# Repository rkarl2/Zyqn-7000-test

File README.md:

# Zynq-7020 Vision Test Board
Test board for the Zynq 7020. This is mainly for my practice/learning more advanced pcb design.

Features:
* USB OTG (Host/Device)
* Ethernet
* On board Programming via JTAG
* HDMI RX
* HDMI TX
* 2x CSI-2 RX
* 1x CSI-2 TX
* 1 Gbit Flash
* SD Card

## Schematics

Full Schmatics [here](./pcb/zynq_test/pdf/Zynqinator.pdf)

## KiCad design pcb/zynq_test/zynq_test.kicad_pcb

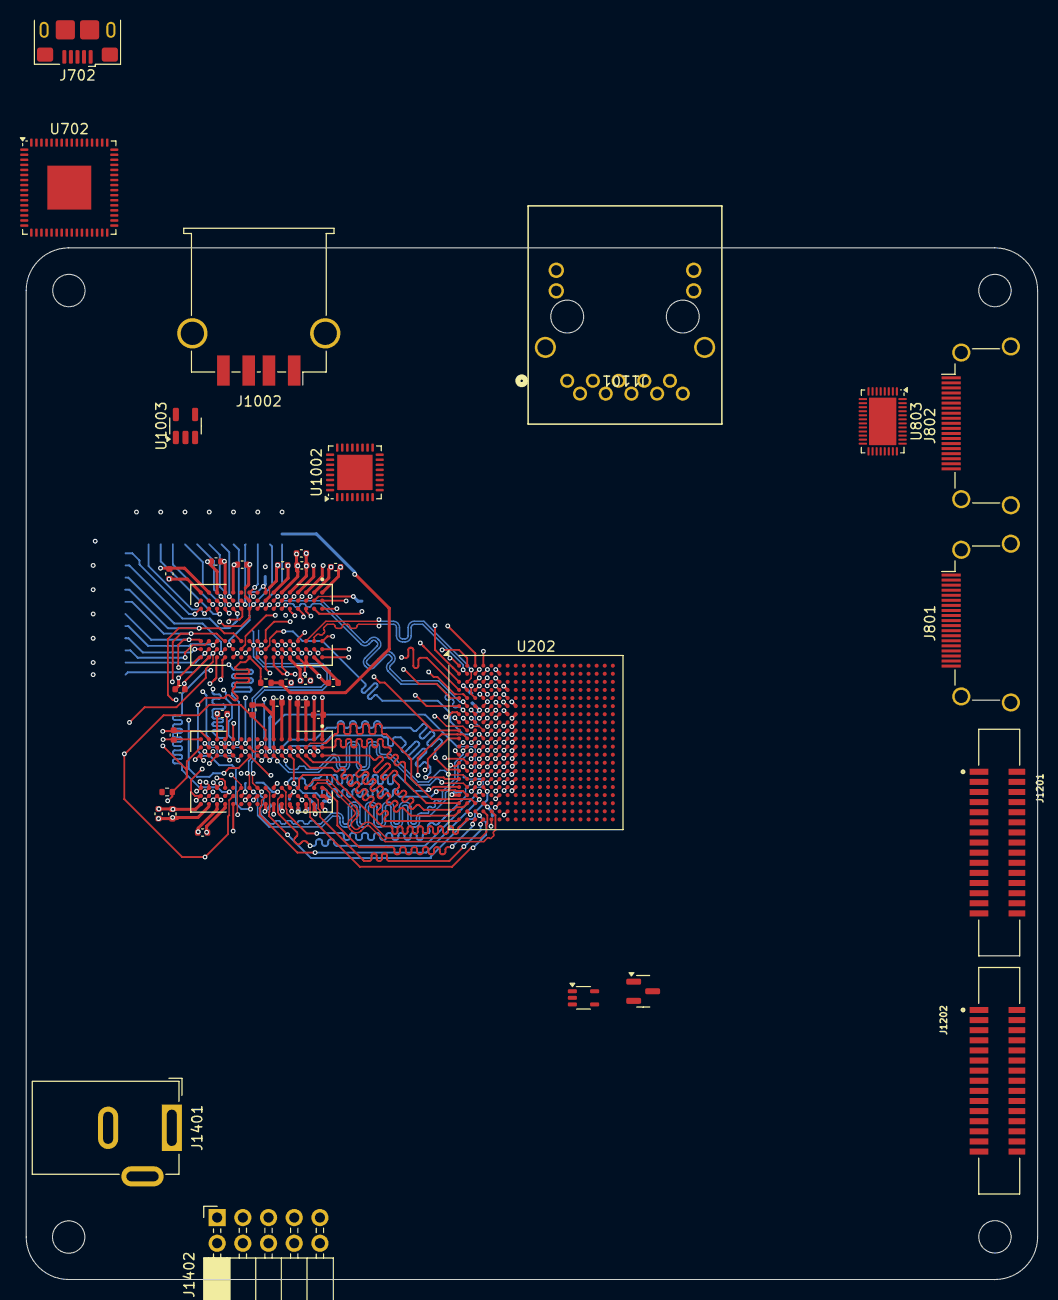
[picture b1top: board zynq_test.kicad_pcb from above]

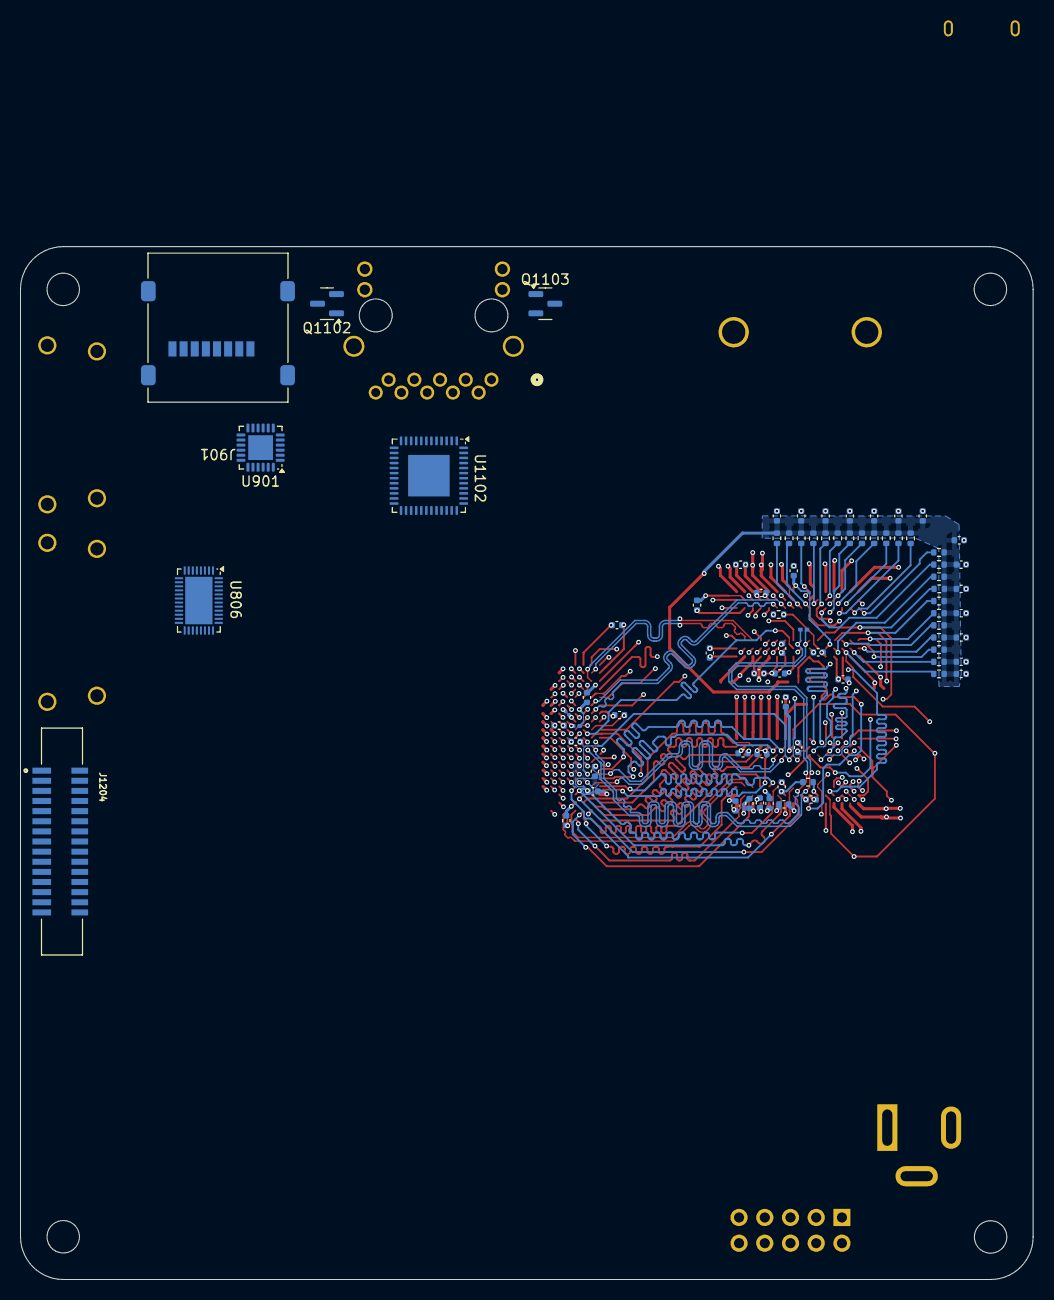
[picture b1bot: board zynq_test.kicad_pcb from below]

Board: 8 copper layers, 100.0 x 102.0 mm, 118 parts (78 on the bottom side), 203 nets.

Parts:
C401, C403, C406, C409, C411, C501, C502, C537, C538, C617, C620, C622, C624: 470n; C_0402_1005Metric
C402, C405, C408, C412, C415, C416, C539, C540, C627, C630: 4u7; C_0402_1005Metric
C404, C407, C410, C413, C414: 100n; C_0402_1005Metric
C503, C504, C505, C506, C507, C508, C509, C510, C511, C512, C513, C514, C515, C516, C517, C518, C519, C520, C521, C522, C523, C524, C525, C526, C527, C528, C530, C532, C533, C534, C535, C536: 47n; C_0402_1005Metric
C529, C531: 10n; C_0402_1005Metric
C632: 100u; C_0402_1005Metric
J702: USB_B_Micro; USB_Micro-B_Amphenol_10118193-0001LF_Horizontal
J801, J802: HDMI_A; HDMI_A_Amphenol_10029449-x01xLF_Horizontal
J901: A-MicroTF-1.85A; microSD_HC_Molex_47219-2001
J1002: USB_A; USB_A_TE_292303-7_Horizontal
J1101: RJ45_JK0654219; ARJM11C7-502-AB-ER2-T_ABR
J1201, J1202, J1204: 1-1734248-5; TE_1-1734248-5
J1401: Barrel_Jack; BarrelJack_GCT_DCJ200-10-A_Horizontal
J1402: Conn_02x05_Odd_Even; PinSocket_2x05_P2.54mm_Horizontal
Q1102, Q1103, Q1104: 2N7002E; SOT-23
R401, R402, R406: 80R; R_0201_0603Metric
R403: 4k7; R_0402_1005Metric
R404, R405: 240R; R_0402_1005Metric
R407, R408, R409, R410, R411, R412, R413, R414, R415, R416, R417, R418, R419, R420, R421, R422, R423, R424, R425, R426, R427, R428, R429, R430: 40R; R_0402_1005Metric
U202: XC7Z020-2CLG400I; Zynq_Z7020-2CLG400I_W_Delay
U401, U402: MT41K256M16TW-107; BGA96C80P9X16_1400X800X120_pinDelays
U702: FT2232HQ; QFN-64-1EP_9x9mm_P0.5mm_EP4.35x4.35mm
U803, U806: TDP1204RNQR; Texas_RNQ0040A_WQFN-40-1EP_6x4mm_P0.4mm_EP4.7x2.7mm
U901: TXS02612RTW; WQFN-24-1EP_4x4mm_P0.5mm_EP2.45x2.45mm
U1002: TUSB1210-Q1; VQFN-32-1EP_5x5mm_P0.5mm_EP3.5x3.5mm
U1003: AP22816AKBWT; SOT-23-5
U1102: LAN8830; VQFN-48-1EP_7x7mm_P0.5mm_EP4.1x4.1mm
U1405: 74LVC1G17; Texas_R-PDSO-G5_DCK-5

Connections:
+1V0: J1402.4, U202.G7 (VCCPINT), U202.G11 (VCCBRAM), U202.G13 (VCCINT), U202.H10 (VCCBRAM), U202.H12 (VCCINT), U202.J7 (VCCPINT), U202.J13 (VCCINT), U202.K12 (VCCINT), U202.L7 (VCCPINT), U202.L13 (VCCINT), U202.M12 (VCCINT), U202.N7 (VCCPINT), U202.N13 (VCCINT), U202.P8 (VCCPINT), U202.P12 (VCCINT), U202.R7 (VCCPINT), U202.R13 (VCCINT)
+1V8: J1402.6, U202.A13 (VCCO_MIO1_501), U202.B16 (VCCO_MIO1_501), U202.D12 (VCCO_MIO1_501), U202.E15 (VCCO_MIO1_501), U202.F8 (VCCPAUX), U202.G9 (VCCPAUX), U202.H8 (VCCPAUX), U202.J9 (VCCADC_0), U202.J11 (VCCAUX), U202.K8 (VCCPAUX), U202.L11 (VCCAUX), U202.M8 (VCCPAUX), U202.N9 (VCCAUX), U202.N11 (VCCAUX), U202.P10 (VCCAUX), U202.R9 (VCCAUX), U202.T8 (VCCO_13), U202.U11 (VCCO_13), U202.W7 (VCCO_13), U202.Y10 (VCCO_13), U901.5 (V_{CCA}), U1002.11 (CS), U1002.14 (CFG), U1002.27 (RESETB), U1002.28 (V_{DD18}), U1002.30 (V_{DD18}), U1002.32 (V_{DDIO}), U1102.17 (VDDIO), U1102.24 (VDDIO), U1102.28 (VDDIO), U1102.35 (VDDIO), U1102.41 (VDDIO)
+1V8_FTDI: U702.12 (VCORE), U702.37 (VCORE), U702.49 (VREGOUT), U702.64 (VCORE)
+1V35: C501.1, C502.1, C503.1, C504.1, C505.1, C506.1, C507.1, C508.1, C509.1, C510.1, C511.1, C512.1, C513.1, C514.1, C515.1, C516.1, C517.1, C518.1, C519.1, C520.1, C521.1, C522.1, C523.1, C524.1, C525.1, C526.1, C527.1, C528.1, C530.1, C532.1, C533.1, C534.1, C535.1, C536.1, C537.1, C538.1, C539.1, C540.1, C617.1, C620.1, C622.1, C624.1, C627.1, C630.1, C632.1, J1402.8, R401.1, U202.A3 (VCCO_DDR_502), U202.D2 (VCCO_DDR_502), U202.E5 (VCCO_DDR_502), U202.G1 (VCCO_DDR_502), U202.H4 (VCCO_DDR_502), U202.L3 (VCCO_DDR_502), U202.P2 (VCCO_DDR_502), U202.R5 (VCCO_DDR_502), U202.U1 (VCCO_DDR_502), U202.V4 (VCCO_DDR_502), U401.A1 (VDDQ), U401.A8 (VDDQ), U401.B2 (VDD), U401.C1 (VDDQ), U401.C9 (VDDQ), U401.D2 (VDDQ), U401.D9 (VDD), U401.E9 (VDDQ), U401.F1 (VDDQ), U401.G7 (VDD), U401.H2 (VDDQ), U401.H9 (VDDQ), U401.K2 (VDD), U401.K8 (VDD), U401.N1 (VDD), U401.N9 (VDD), U401.R1 (VDD), U401.R9 (VDD), U402.A1 (VDDQ), U402.A8 (VDDQ), U402.B2 (VDD), U402.C1 (VDDQ), U402.C9 (VDDQ), U402.D2 (VDDQ), U402.D9 (VDD), U402.E9 (VDDQ), U402.F1 (VDDQ), U402.G7 (VDD), U402.H2 (VDDQ), U402.H9 (VDDQ), U402.K2 (VDD), U402.K8 (VDD), U402.N1 (VDD), U402.N9 (VDD), U402.R1 (VDD), U402.R9 (VDD)
+3V3: J901.4 (VDD), J1101.11 (L_LED_A), J1101.13 (R_LED_A), J1201.15, J1201.15_1 (15__1), J1202.15, J1202.15_1 (15__1), J1204.15, J1204.15_1 (15__1), J1402.10, U202.B6 (VCCO_MIO0_500), U202.C19 (VCCO_35), U202.D7 (VCCO_MIO0_500), U202.F18 (VCCO_35), U202.H14 (VCCO_35), U202.J17 (VCCO_35), U202.K6 (VCCO_0), U202.K20 (VCCO_35), U202.M6 (CFGBVS_0), U202.M16 (VCCO_35), U202.N6 (RSVDVCC3), U202.N19 (VCCO_34), U202.R6 (RSVDVCC2), U202.R15 (VCCO_34), U202.T6 (RSVDVCC1), U202.T18 (VCCO_34), U202.V14 (VCCO_34), U202.W17 (VCCO_34), U202.Y20 (VCCO_34), U702.20 (VCCIO), U702.31 (VCCIO), U702.42 (VCCIO), U702.50 (VREGIN), U702.56 (VCCIO), U803.1 (VCC), U803.6 (VCC), U803.14 (VIO), U803.20 (VCC), U803.28 (VCC), U806.1 (VCC), U806.6 (VCC), U806.14 (VIO), U806.20 (VCC), U806.28 (VCC), U901.17 (VCC_{B1}), U901.21 (VCC_{B0}), U1002.20 (V_{DD33}), U1002.21 (V_{BAT}), U1405.5 (VCC)
+5V: J801.18 (+5V), J802.18 (+5V), J1402.2, U1003.3 (IN)
+5V_{USB_OTG}: J1002.1 (VBUS), U1002.22 (V_{BUS}), U1003.1 (OUT), U1003.5 (OUT)
+V_{TT} 0V675: C402.1, C403.1, C404.1, C405.1, C406.1, C407.1, C408.1, C409.1, C410.1, C411.1, C412.1, C413.1, C414.1, C415.1, C416.1, R407.1, R408.1, R409.1, R410.1, R411.1, R412.1, R413.1, R414.1, R415.1, R416.1, R417.1, R418.1, R419.1, R420.1, R421.1, R422.1, R423.1, R424.1, R425.1, R426.1, R427.1, R428.1, R429.1, R430.1
/Boot/SD0.CLK: J901.5 (CLK), U901.9 (CLKA), U901.19 (CLK_{B0})
/Boot/SD0.CMD: J901.3 (CMD), U202.C17 (PS_MIO41_501), U901.4 (CMDA), U901.20 (CMD_{B0})
/Boot/SD0.DAT0: J901.7 (DAT0), U901.18 (DAT0_{B0})
/Boot/SD0.DAT1: J901.8 (DAT1), U901.16 (DAT1_{B0})
/Boot/SD0.DAT2: J901.1 (DAT2), U901.23 (DAT2_{B0})
/Boot/SD0.DAT3: J901.2 (DAT3/CD), U901.22 (DAT3_{B0})
/Boot/SD0.DATA-0: U202.E12 (PS_MIO42_501), U901.6 (DAT0A)
/Boot/SD0.DATA-1: U202.A9 (PS_MIO43_501), U901.7 (DAT1A)
/Boot/SD0.DATA-2: U202.F13 (PS_MIO44_501), U901.1 (DAT2A)
/Boot/SD0.DATA-3: U202.B15 (PS_MIO45_501), U901.3 (DAT3A)
/Cameras/CAM0.GPIO1.: J1201.11, J1201.11_1 (11__1), J1201.12, J1201.12_1 (12__1)
/Cameras/CAM1.GPIO1.: J1202.11, J1202.11_1 (11__1), J1202.12, J1202.12_1 (12__1)
/Cameras/CAM2.GPIO1.: J1204.11, J1204.11_1 (11__1), J1204.12, J1204.12_1 (12__1)
/Cameras/CAM2.TX.0_N: J1204.2, J1204.2_1 (2__1)
/Cameras/CAM2.TX.0_P: J1204.3, J1204.3_1 (3__1)
/Cameras/CAM2.TX.1_N: J1204.5, J1204.5_1 (5__1)
/Cameras/CAM2.TX.1_P: J1204.6, J1204.6_1 (6__1)
/Cameras/CAM2.TX.CLK_N: J1204.8, J1204.8_1 (8__1)
/Cameras/CAM2.TX.CLK_P: J1204.9, J1204.9_1 (9__1)
/Cameras/CAM_RX.0.CAM_CLK_N: J1201.8, J1201.8_1 (8__1), U202.L20 (IO_L9N_T1_DQS_AD3N_35)
/Cameras/CAM_RX.0.CAM_CLK_P: J1201.9, J1201.9_1 (9__1), U202.L19 (IO_L9P_T1_DQS_AD3P_35)
/Cameras/CAM_RX.0.CAM_D0_N: J1201.2, J1201.2_1 (2__1), U202.F20 (IO_L15N_T2_DQS_AD12N_35)
/Cameras/CAM_RX.0.CAM_D0_P: J1201.3, J1201.3_1 (3__1), U202.F19 (IO_L15P_T2_DQS_AD12P_35)
/Cameras/CAM_RX.0.CAM_D1_N: J1201.5, J1201.5_1 (5__1), U202.H20 (IO_L17N_T2_AD5N_35)
/Cameras/CAM_RX.0.CAM_D1_P: J1201.6, J1201.6_1 (6__1), U202.J20 (IO_L17P_T2_AD5P_35)
/Cameras/CAM_RX.0.I2C_CLK: J1201.13, J1201.13_1 (13__1), U202.K17 (IO_L12P_T1_MRCC_35)
/Cameras/CAM_RX.0.I2C_SDA: J1201.14, J1201.14_1 (14__1), U202.K18 (IO_L12N_T1_MRCC_35)
/Cameras/CAM_RX.1.CAM_CLK_N: J1202.8, J1202.8_1 (8__1), U202.W15 (IO_L10N_T1_34)
/Cameras/CAM_RX.1.CAM_CLK_P: J1202.9, J1202.9_1 (9__1), U202.V15 (IO_L10P_T1_34)
/Cameras/CAM_RX.1.CAM_D0_N: J1202.2, J1202.2_1 (2__1), U202.Y19 (IO_L17N_T2_34)
/Cameras/CAM_RX.1.CAM_D0_P: J1202.3, J1202.3_1 (3__1), U202.Y18 (IO_L17P_T2_34)
/Cameras/CAM_RX.1.CAM_D1_N: J1202.5, J1202.5_1 (5__1), U202.Y17 (IO_L7N_T1_34)
/Cameras/CAM_RX.1.CAM_D1_P: J1202.6, J1202.6_1 (6__1), U202.Y16 (IO_L7P_T1_34)
/Cameras/CAM_RX.1.I2C_CLK: J1202.13, J1202.13_1 (13__1), U202.V20 (IO_L16P_T2_34)
/Cameras/CAM_RX.1.I2C_SDA: J1202.14, J1202.14_1 (14__1), U202.W20 (IO_L16N_T2_34)
/Cameras/CAM_TX.2.I2C_CLK: J1204.13, J1204.13_1 (13__1), U202.T14 (IO_L5P_T0_34)
/Cameras/CAM_TX.2.I2C_SDA: J1204.14, J1204.14_1 (14__1), U202.T15 (IO_L5N_T0_34)
/ETHERNET/ETH0.MDC: U202.C10 (PS_MIO52_501), U1102.37 (MDC)
/ETHERNET/ETH0.MDIO: U202.C11 (PS_MIO53_501), U1102.38 (MDIO)
/ETHERNET/ETH0_INT: U202.K14 (IO_L20P_T3_AD6P_35), U1102.39 (INT_N/GPIO5)
/ETHERNET/ETH_1V1: U1102.4 (VDDAL), U1102.9 (VDDAL), U1102.47 (VDDAL_PLL)
/ETHERNET/ETH_A_3V3: U1102.1 (VDDAH), U1102.12 (VDDAH)
/ETHERNET/ETH_TX1_N: J1101.2 (TRD1-), U1102.3 (TXRXM_A)
/ETHERNET/ETH_TX1_P: J1101.1 (TRD1+), U1102.2 (TXRXP_A)
/ETHERNET/ETH_TX2_N: J1101.4 (TRD2-), U1102.6 (TXRXM_B)
/ETHERNET/ETH_TX2_P: J1101.3 (TRD2+), U1102.5 (TXRXP_B)
/ETHERNET/ETH_TX3_N: J1101.8 (TRD3-), U1102.8 (TXRXM_C)
/ETHERNET/ETH_TX3_P: J1101.7 (TRD3+), U1102.7 (TXRXP_C)
/ETHERNET/ETH_TX4_N: J1101.10 (TRD4-), U1102.11 (TXRXM_D)
/ETHERNET/ETH_TX4_P: J1101.9 (TRD4+), U1102.10 (TXRXP_D)
/ETHERNET/ETH_VDD_1V1: U1102.23 (VDD), U1102.27 (VDD), U1102.31 (VDD), U1102.40 (VDD)
/HDMI/HDMI.CTR.SCL: U202.J16 (IO_L24N_T3_AD15N_35), U803.21 (SCL/CFG0), U806.21 (SCL/CFG0)
/HDMI/HDMI.CTR.SDA: U202.K16 (IO_L24P_T3_AD15P_35), U803.22 (SDA/CFG1), U806.22 (SDA/CFG1)
/HDMI/HDMI.EN: U202.L16 (IO_L11P_T1_SRCC_35), U803.7 (EN), U806.7 (EN)
/HDMI/HDMI.RX.CLK_N: U202.G18 (IO_L16N_T2_35), U806.30 (OUT_CLKN)
/HDMI/HDMI.RX.CLK_P: U202.G17 (IO_L16P_T2_35), U806.31 (OUT_CLKP)
/HDMI/HDMI.RX.D0_N: U202.G15 (IO_L19N_T3_VREF_35), U806.33 (OUT_D0N)
/HDMI/HDMI.RX.D0_P: U202.H15 (IO_L19P_T3_35), U806.34 (OUT_D0P)
/HDMI/HDMI.RX.D1_N: U202.F17 (IO_L6N_T0_VREF_35), U806.36 (OUT_D1N)
/HDMI/HDMI.RX.D1_P: U202.F16 (IO_L6P_T0_35), U806.37 (OUT_D1P)
/HDMI/HDMI.RX.D2_N: U202.D18 (IO_L3N_T0_DQS_AD1N_35), U806.39 (OUT_D2N)
/HDMI/HDMI.RX.D2_P: U202.E17 (IO_L3P_T0_DQS_AD1P_35), U806.40 (OUT_D2P)
/HDMI/HDMI.RX.SCL: U202.J18 (IO_L14P_T2_AD4P_SRCC_35), U806.24 (LV_DDC_SCL)
/HDMI/HDMI.RX.SDA: U202.H18 (IO_L14N_T2_AD4N_SRCC_35), U806.25 (LV_DDC_SDA)
/HDMI/HDMI.TX.CLK_N: U202.E19 (IO_L5N_T0_AD9N_35), U803.19 (IN_CLKN)
/HDMI/HDMI.TX.CLK_P: U202.E18 (IO_L5P_T0_AD9P_35), U803.18 (IN_CLKP)
/HDMI/HDMI.TX.D0_N: U202.D20 (IO_L4N_T0_35), U803.16 (IN_D0N)
/HDMI/HDMI.TX.D0_P: U202.D19 (IO_L4P_T0_35), U803.15 (IN_D0P)
/HDMI/HDMI.TX.D1_N: U202.B20 (IO_L1N_T0_AD0N_35), U803.13 (IN_D1N)
/HDMI/HDMI.TX.D1_P: U202.C20 (IO_L1P_T0_AD0P_35), U803.12 (IN_D1P)
/HDMI/HDMI.TX.D2_N: U202.A20 (IO_L2N_T0_AD8N_35), U803.10 (IN_D2N)
/HDMI/HDMI.TX.D2_P: U202.B19 (IO_L2P_T0_AD8P_35), U803.9 (IN_D2P)
/HDMI/HDMI.TX.HDP: U202.J14 (IO_L20N_T3_AD6N_35), U803.32 (HPD_IN)
/HDMI/HDMI.TX.SCL: U202.G14 (IO_0_35), U803.24 (LV_DDC_SCL)
/HDMI/HDMI.TX.SDA: U202.J15 (IO_25_35), U803.25 (LV_DDC_SDA)
/HDMI/HDMI_SHIELD: J801.SH, J802.SH
/Power/PWR_ON_RST: Q1104.1 (G), U202.C7 (PS_POR_B_500), U1405.4
/Programmer/FTDI_D+: J702.3 (D+), U702.8 (DP)
/Programmer/FTDI_D-: J702.2 (D-), U702.7 (DM)
/USB_OTG/USB0.DATA-0: U202.A14 (PS_MIO32_501), U1002.3 (DATA0)
/USB_OTG/USB0.DATA-1: U202.D15 (PS_MIO33_501), U1002.4 (DATA1)
/USB_OTG/USB0.DATA-2: U202.A12 (PS_MIO34_501), U1002.5 (DATA2)
/USB_OTG/USB0.DATA-3: U202.F12 (PS_MIO35_501), U1002.6 (DATA3)
/USB_OTG/USB0.DATA-4: U202.C16 (PS_MIO28_501), U1002.7 (DATA4)
/USB_OTG/USB0.DATA-5: U202.A10 (PS_MIO37_501), U1002.9 (DATA5)
/USB_OTG/USB0.DATA-6: U202.E13 (PS_MIO38_501), U1002.10 (DATA6)
/USB_OTG/USB0.DATA-7: U202.C18 (PS_MIO39_501), U1002.13 (DATA7)
/USB_OTG/USB0.DIR: U202.C13 (PS_MIO29_501), U1002.31 (DIR)
/USB_OTG/USB0.NXT: U202.E16 (PS_MIO31_501), U1002.2 (NXT)
/USB_OTG/USB0.STP: U202.C15 (PS_MIO30_501), U1002.29 (STP)
/USB_OTG/USB_OTG.D+: J1002.3 (D+), U1002.18 (DP)
/USB_OTG/USB_OTG.D-: J1002.2 (D-), U1002.19 (DM)
/Zynq Dram/DDR_ADDR0: R407.2, U202.N2 (PS_DDR_A0_502), U401.N3 (A0), U402.N3 (A0)
/Zynq Dram/DDR_ADDR1: R409.2, U202.K2 (PS_DDR_A1_502), U401.P7 (A1), U402.P7 (A1)
/Zynq Dram/DDR_ADDR2: R412.2, U202.M3 (PS_DDR_A2_502), U401.P3 (A2), U402.P3 (A2)
/Zynq Dram/DDR_ADDR3: R415.2, U202.K3 (PS_DDR_A3_502), U401.N2 (A3), U402.N2 (A3)
/Zynq Dram/DDR_ADDR4: R418.2, U202.M4 (PS_DDR_A4_502), U401.P8 (A4), U402.P8 (A4)
/Zynq Dram/DDR_ADDR5: R421.2, U202.L1 (PS_DDR_A5_502), U401.P2 (A5), U402.P2 (A5)
/Zynq Dram/DDR_ADDR6: R424.2, U202.L4 (PS_DDR_A6_502), U401.R8 (A6), U402.R8 (A6)
/Zynq Dram/DDR_ADDR7: R427.2, U202.K4 (PS_DDR_A7_502), U401.R2 (A7), U402.R2 (A7)
/Zynq Dram/DDR_ADDR8: R408.2, U202.K1 (PS_DDR_A8_502), U401.T8 (A8), U402.T8 (A8)
/Zynq Dram/DDR_ADDR9: R410.2, U202.J4 (PS_DDR_A9_502), U401.R3 (A9), U402.R3 (A9)
/Zynq Dram/DDR_ADDR10: R413.2, U202.F5 (PS_DDR_A10_502), U401.L7 (A10/AP), U402.L7 (A10/AP)
/Zynq Dram/DDR_ADDR11: R416.2, U202.G4 (PS_DDR_A11_502), U401.R7 (A11), U402.R7 (A11)
/Zynq Dram/DDR_ADDR12: R419.2, U202.E4 (PS_DDR_A12_502), U401.N7 (A12/~BC), U402.N7 (A12/~BC)
/Zynq Dram/DDR_ADDR13: R422.2, U202.D4 (PS_DDR_A13_502), U401.T3 (A13), U402.T3 (A13)
/Zynq Dram/DDR_ADDR14: R425.2, U202.F4 (PS_DDR_A14_502), U401.T7 (A14), U402.T7 (A14)
/Zynq Dram/DDR_CTR.BA0: R428.2, U202.L5 (PS_DDR_BA0_502), U401.M2 (BA0), U402.M2 (BA0)
/Zynq Dram/DDR_CTR.BA1: R429.2, U202.R4 (PS_DDR_BA1_502), U401.N8 (BA1), U402.N8 (BA1)
/Zynq Dram/DDR_CTR.BA2: R430.2, U202.J5 (PS_DDR_BA2_502), U401.M3 (BA2), U402.M3 (BA2)
/Zynq Dram/DDR_CTR.CAS: R414.2, U202.P5 (PS_DDR_CAS_B_502), U401.K3 (~CAS), U402.K3 (~CAS)
/Zynq Dram/DDR_CTR.CLK_E: R411.2, U202.N3 (PS_DDR_CKE_502), U401.K9 (CKE), U402.K9 (CKE)
/Zynq Dram/DDR_CTR.CLK_N: R406.2, U202.M2 (PS_DDR_CKN_502), U401.K7 (~CK), U402.K7 (~CK)
/Zynq Dram/DDR_CTR.CLK_P: R406.1, U202.L2 (PS_DDR_CKP_502), U401.J7 (CK), U402.J7 (CK)
/Zynq Dram/DDR_CTR.CS: R417.2, U202.N1 (PS_DDR_CS_B_502), U401.L2 (~CS), U402.L2 (~CS)
/Zynq Dram/DDR_CTR.ODT: R420.2, U202.N5 (PS_DDR_ODT_502), U401.K1 (ODT), U402.K1 (ODT)
/Zynq Dram/DDR_CTR.RAS: R423.2, U202.P4 (PS_DDR_RAS_B_502), U401.J3 (~RAS), U402.J3 (~RAS)
/Zynq Dram/DDR_CTR.RST: R403.1, U202.B4 (PS_DDR_DRST_B_502), U401.T2 (~RESET), U402.T2 (~RESET)
/Zynq Dram/DDR_CTR.WE: R426.2, U202.M5 (PS_DDR_WE_B_502), U401.L3 (~WE), U402.L3 (~WE)
/Zynq Dram/DDR_L0.0: U202.C3 (PS_DDR_DQ0_502), U401.D7 (DQ8)
/Zynq Dram/DDR_L0.1: U202.B3 (PS_DDR_DQ1_502), U401.A2 (DQ13)
/Zynq Dram/DDR_L0.2: U202.A2 (PS_DDR_DQ2_502), U401.A3 (DQ15)
/Zynq Dram/DDR_L0.3: U202.A4 (PS_DDR_DQ3_502), U401.C2 (DQ11)
/Zynq Dram/DDR_L0.4: U202.D3 (PS_DDR_DQ4_502), U401.B8 (DQ14)
/Zynq Dram/DDR_L0.5: U202.D1 (PS_DDR_DQ5_502), U401.A7 (DQ12)
/Zynq Dram/DDR_L0.6: U202.C1 (PS_DDR_DQ6_502), U401.C3 (DQ9)
/Zynq Dram/DDR_L0.7: U202.E1 (PS_DDR_DQ7_502), U401.C8 (DQ10)
/Zynq Dram/DDR_L0.DM: U202.A1 (PS_DDR_DM0_502), U401.D3 (UDM)
/Zynq Dram/DDR_L0.DQS_N: U202.B2 (PS_DDR_DQS_N0_502), U401.B7 (~UDQS)
/Zynq Dram/DDR_L0.DQS_P: U202.C2 (PS_DDR_DQS_P0_502), U401.C7 (UDQS)
/Zynq Dram/DDR_L1.8: U202.E2 (PS_DDR_DQ8_502), U401.H3 (DQ4)
/Zynq Dram/DDR_L1.9: U202.E3 (PS_DDR_DQ9_502), U401.G2 (DQ6)
/Zynq Dram/DDR_L1.10: U202.G3 (PS_DDR_DQ10_502), U401.F2 (DQ2)
/Zynq Dram/DDR_L1.11: U202.H3 (PS_DDR_DQ11_502), U401.E3 (DQ0)
/Zynq Dram/DDR_L1.12: U202.J3 (PS_DDR_DQ12_502), U401.H8 (DQ5)
/Zynq Dram/DDR_L1.13: U202.H2 (PS_DDR_DQ13_502), U401.F7 (DQ1)
/Zynq Dram/DDR_L1.14: U202.H1 (PS_DDR_DQ14_502), U401.F8 (DQ3)
/Zynq Dram/DDR_L1.15: U202.J1 (PS_DDR_DQ15_502), U401.H7 (DQ7)
/Zynq Dram/DDR_L1.DM: U202.F1 (PS_DDR_DM1_502), U401.E7 (LDM)
/Zynq Dram/DDR_L1.DQS_N: U202.F2 (PS_DDR_DQS_N1_502), U401.G3 (~LDQS)
/Zynq Dram/DDR_L1.DQS_P: U202.G2 (PS_DDR_DQS_P1_502), U401.F3 (LDQS)
/Zynq Dram/DDR_L2.16: U202.P1 (PS_DDR_DQ16_502), U402.G2 (DQ6)
/Zynq Dram/DDR_L2.17: U202.P3 (PS_DDR_DQ17_502), U402.H3 (DQ4)
/Zynq Dram/DDR_L2.18: U202.R3 (PS_DDR_DQ18_502), U402.F7 (DQ1)
/Zynq Dram/DDR_L2.19: U202.R1 (PS_DDR_DQ19_502), U402.F2 (DQ2)
/Zynq Dram/DDR_L2.20: U202.T4 (PS_DDR_DQ20_502), U402.H7 (DQ7)
/Zynq Dram/DDR_L2.21: U202.U4 (PS_DDR_DQ21_502), U402.F8 (DQ3)
/Zynq Dram/DDR_L2.22: U202.U2 (PS_DDR_DQ22_502), U402.E3 (DQ0)
/Zynq Dram/DDR_L2.23: U202.U3 (PS_DDR_DQ23_502), U402.H8 (DQ5)
/Zynq Dram/DDR_L2.DM: U202.T1 (PS_DDR_DM2_502), U402.E7 (LDM)
/Zynq Dram/DDR_L2.DQS_N: U202.T2 (PS_DDR_DQS_N2_502), U402.G3 (~LDQS)
/Zynq Dram/DDR_L2.DQS_P: U202.R2 (PS_DDR_DQS_P2_502), U402.F3 (LDQS)
/Zynq Dram/DDR_L3.24: U202.V1 (PS_DDR_DQ24_502), U402.A2 (DQ13)
/Zynq Dram/DDR_L3.25: U202.Y3 (PS_DDR_DQ25_502), U402.A7 (DQ12)
/Zynq Dram/DDR_L3.26: U202.W1 (PS_DDR_DQ26_502), U402.C3 (DQ9)
/Zynq Dram/DDR_L3.27: U202.Y4 (PS_DDR_DQ27_502), U402.B8 (DQ14)
/Zynq Dram/DDR_L3.28: U202.Y2 (PS_DDR_DQ28_502), U402.D7 (DQ8)
/Zynq Dram/DDR_L3.29: U202.W3 (PS_DDR_DQ29_502), U402.C8 (DQ10)
/Zynq Dram/DDR_L3.30: U202.V2 (PS_DDR_DQ30_502), U402.A3 (DQ15)
/Zynq Dram/DDR_L3.31: U202.V3 (PS_DDR_DQ31_502), U402.C2 (DQ11)
/Zynq Dram/DDR_L3.DM: U202.Y1 (PS_DDR_DM3_502), U402.D3 (UDM)
/Zynq Dram/DDR_L3.DQS_N: U202.W5 (PS_DDR_DQS_P3_502), U402.B7 (~UDQS)
/Zynq Dram/DDR_L3.DQS_P: U202.W4 (PS_DDR_DQS_N3_502), U402.C7 (UDQS)
/Zynq FPGA/CLK_125M: U202.H16 (IO_L13P_T2_MRCC_35), U1102.42 (CLK125_NDO/GPIO6/LED_MODE)
GND: C401.2, C402.2, C403.2, C404.2, C405.2, C406.2, C407.2, C408.2, C409.2, C410.2, C411.2, C412.2, C413.2, C414.2, C415.2, C416.2, C501.2, C502.2, C503.2, C504.2, C505.2, C506.2, C507.2, C508.2, C509.2, C510.2, C511.2, C512.2, C513.2, C514.2, C515.2, C516.2, C517.2, C518.2, C519.2, C520.2, C521.2, C522.2, C523.2, C524.2, C525.2, C526.2, C527.2, C528.2, C529.2, C530.2, C531.2, C532.2, C533.2, C534.2, C535.2, C536.2, C537.2, C538.2, C539.2, C540.2, C617.2, C620.2, C622.2, C624.2, C627.2, C630.2, C632.2, J702.5 (GND), J801.2 (D2S), J801.5 (D1S), J801.8 (D0S), J801.11 (CKS), J801.17 (GND), J802.2 (D2S), J802.5 (D1S), J802.8 (D0S), J802.11 (CKS), J802.17 (GND), J901.6 (VSS), J1002.4 (GND), J1002.5 (Shield), J1201.1, J1201.1_1 (1__1), J1201.4, J1201.4_1 (4__1), J1201.7, J1201.7_1 (7__1), J1201.10, J1201.10_1 (10__1), J1202.1, J1202.1_1 (1__1), J1202.4, J1202.4_1 (4__1), J1202.7, J1202.7_1 (7__1), J1202.10, J1202.10_1 (10__1), J1204.1, J1204.1_1 (1__1), J1204.4, J1204.4_1 (4__1), J1204.7, J1204.7_1 (7__1), J1204.10, J1204.10_1 (10__1), J1401.2, Q1102.2 (S), Q1103.2 (S), Q1104.2 (S), R402.2, R403.2, R404.2, R405.2, U202.A8 (GND), U202.A18 (GND), U202.B1 (GND), U202.B11 (GND), U202.C4 (GND), U202.C9 (GND), U202.C14 (GND), U202.D17 (GND), U202.E10 (GND), U202.E20 (GND), U202.F3 (GND), U202.F7 (GND), U202.F10 (RSVDGND), U202.F11 (VCCBATT_0), U202.G10 (GND), U202.G12 (GND), U202.G16 (GND), U202.H7 (GND), U202.H9 (GND), U202.H11 (GND), U202.H13 (GND), U202.H19 (GND), U202.J2 (GND), U202.J8 (GND), U202.J10 (GNDADC_0), U202.J12 (GND), U202.K5 (GND), U202.K7 (GND), U202.K10 (VREFN_0), U202.K11 (GND), U202.K13 (GND), U202.K15 (GND), U202.L8 (GND), U202.L9 (VREFP_0), U202.L10 (VN_0), U202.L12 (GND), U202.L18 (GND), U202.M1 (GND), U202.M7 (GND), U202.M9 (DXP_0), U202.M10 (DXN_0), U202.M11 (GND), U202.M13 (GND), U202.N4 (GND), U202.N8 (GND), U202.N10 (GND), U202.N12 (GND), U202.N14 (GND), U202.P7 (GND), U202.P9 (GND), U202.P11 (GND), U202.P13 (GND), U202.P17 (GND), U202.R8 (GND), U202.R12 (GND), U202.R20 (GND), U202.T3 (GND), U202.T7 (GND), U202.T13 (GND), U202.U6 (GND), U202.U16 (GND), U202.V9 (GND), U202.V19 (GND), U202.W2 (GND), U202.W12 (GND), U202.Y5 (GND), U202.Y15 (GND), U401.A9 (VSS), U401.B1 (VSSQ), U401.B3 (VSS), U401.B9 (VSSQ), U401.D1 (VSSQ), U401.D8 (VSSQ), U401.E1 (VSS), U401.E2 (VSSQ), U401.E8 (VSSQ), U401.F9 (VSSQ), U401.G1 (VSSQ), U401.G8 (VSS), U401.G9 (VSSQ), U401.J2 (VSS), U401.J8 (VSS), U401.M1 (VSS), U401.M9 (VSS), U401.P1 (VSS), U401.P9 (VSS), U401.T1 (VSS), U401.T9 (VSS), U402.A9 (VSS), U402.B1 (VSSQ), U402.B3 (VSS), U402.B9 (VSSQ), U402.D1 (VSSQ), U402.D8 (VSSQ), U402.E1 (VSS), U402.E2 (VSSQ), U402.E8 (VSSQ), U402.F9 (VSSQ), U402.G1 (VSSQ), U402.G8 (VSS), U402.G9 (VSSQ), U402.J2 (VSS), U402.J8 (VSS), U402.M1 (VSS), U402.M9 (VSS), U402.P1 (VSS), U402.P9 (VSS), U402.T1 (VSS), U402.T9 (VSS), U702.1 (GND), U702.5 (GND), U702.10 (AGND), U702.11 (GND), U702.13 (TEST), U702.15 (GND), U702.25 (GND), U702.35 (GND), U702.47 (GND), U702.51 (GND), U702.65 (GND), U803.41 (GND), U806.41 (GND), U901.2 (GND), U901.11 (GND), U901.25 (EPAD), U1002.33 (GND), U1003.2 (GND), U1102.49 (GND), U1405.3 (GND)
unnamed: J1101.17 (Sh), J1101.18 (Sh)
unnamed: J801.10 (CK+), U806.18 (IN_CLKP)
unnamed: J801.12 (CK-), U806.19 (IN_CLKN)
unnamed: J801.7 (D0+), U806.15 (IN_D0P)
unnamed: J801.9 (D0-), U806.16 (IN_D0N)
unnamed: J801.4 (D1+), U806.12 (IN_D1P)
unnamed: J801.6 (D1-), U806.13 (IN_D1N)
unnamed: J801.1 (D2+), U806.9 (IN_D2P)
unnamed: J801.3 (D2-), U806.10 (IN_D2N)
unnamed: J801.19 (HPD), U806.32 (HPD_IN)
unnamed: J801.15 (SCL), U806.27 (HV_DDC_SCL)
unnamed: J801.16 (SDA), U806.26 (HV_DDC_SDA)
unnamed: J802.10 (CK+), U803.31 (OUT_CLKP)
unnamed: J802.12 (CK-), U803.30 (OUT_CLKN)
unnamed: J802.7 (D0+), U803.34 (OUT_D0P)
unnamed: J802.9 (D0-), U803.33 (OUT_D0N)
unnamed: J802.4 (D1+), U803.37 (OUT_D1P)
unnamed: J802.6 (D1-), U803.36 (OUT_D1N)
unnamed: J802.1 (D2+), U803.40 (OUT_D2P)
unnamed: J802.3 (D2-), U803.39 (OUT_D2N)
unnamed: J802.19 (HPD), U803.11 (HPD_OUT)
unnamed: J802.15 (SCL), U803.27 (HV_DDC_SCL)
unnamed: J802.16 (SDA), U803.26 (HV_DDC_SDA)
unnamed: J1101.5 (TRCT1), J1101.6 (TRCT2)
unnamed: R401.2, U202.G5 (PS_DDR_VRN_502)
unnamed: R402.1, U202.H5 (PS_DDR_VRP_502)
unnamed: R404.1, U401.L8 (ZQ)
unnamed: R405.1, U402.L8 (ZQ)
unnamed: U1002.17 (CPEN), U1003.4 (EN)
V_{TT 0.675} REF: C401.1, C529.1, C531.1, U202.H6 (PS_DDR_VREF0_502), U202.P6 (PS_DDR_VREF1_502), U401.H1 (VREFDQ), U401.M8 (VREFCA), U402.H1 (VREFDQ), U402.M8 (VREFCA)

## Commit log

2025-08-18 Almost done with PS MIO config
2025-08-21 Changed MIO signals to Buses
2025-08-23 Finished PS, started on PWR
2025-08-23 Finished FPGA decouploing, and jtag programmer
2025-08-24 Finished boot media, added structure for IO
2025-08-27 Added Cameras, changed SD card IC for skew reasons
2025-08-31 Finished USB, started om ETH PHY
2025-09-01 Finished Ethernet, swapped FTDI chip for QFN
2025-09-01 Finished HDMI
2025-09-03 Started on DDR3
2025-09-08 Connected DDR3, cleaned up some thing
2025-09-14 Finished Power Supply
2025-09-14 Finished most of the schematic, will start routing soon
2025-10-03 Finished to first ddr ic
2025-10-05 DDR routed
2025-10-25 finished diff of HDMI
2025-11-16 Almost done with BOM
2025-11-17 Added pdf Schematics, updated readme
2025-11-26 Version sent to JLCPCB
2025-11-26 Updated readme with schematics
2025-11-26 Fixed top view
